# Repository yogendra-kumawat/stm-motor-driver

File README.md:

# MotorCore-32 v1.0
### STM32 Motor Control Carrier Board

> A modular carrier board for the Blue Pill STM32F103 module — dual DRV8833 H-bridge motor drivers, onboard power management, fault indication, and full GPIO breakout. Designed for robotics, automation, and embedded motor control projects.

---

## Board Preview

<!--  board photos -->
```
[ Top view photo ]         [ Bottom view photo ]
```
> *Photos will be added after fabrication*

---

## Features

| Feature | Details |
|---|---|
| MCU Module | Blue Pill (STM32F103C8T6) via female headers |
| Motor Drivers | 2× DRV8833PW — 1.5A per channel, dual H-bridge |
| Motor Outputs | 4× 2-pin screw terminals |
| 3.3V Rail | AMS1117-3.3 onboard regulator |
| Adjustable Rail | LM317 with external resistor headers |
| Input Voltage | 9V DC, 2A minimum |
| Reverse Polarity | 1N4007 diode protection |
| Spike Protection | SMBJ9.0CA TVS diode |
| Fault Indication | nFAULT LED per DRV8833 |
| GPIO Breakout | 2× 20-pin male headers — full Blue Pill pin access |

---

## Pin Map

### Power Rails

| Rail | Source | Voltage | Max Current |
|---|---|---|---|
| VMOT | Direct input after TVS | 9V | Input limited |
| 3.3V | AMS1117-3.3 | 3.3V | 800mA |
| VADJ | LM317 adjustable | User set | 1.5A |
| GND | Common ground | 0V | — |

### LM317 Adjust Header (J_ADJ)

| Pin | Signal |
|---|---|
| 1 | OUT |
| 2 | ADJ |
| 3 | R1 (connect 240Ω) |
| 4 | GND (connect R2 here) |

**Vout formula:** `Vout = 1.25 × (1 + R2/R1)`

| R2 | Vout (R1 = 240Ω) |
|---|---|
| 470Ω | 3.7V |
| 750Ω | 5.0V |
| 1.2kΩ | 7.5V |
| 1.5kΩ | 9.0V |

### DRV8833 Motor Driver 1 (U1)

| Pin | Signal | Connect to |
|---|---|---|
| IN1 | Motor A direction 1 | STM32 PWM pin |
| IN2 | Motor A direction 2 | STM32 PWM pin |
| IN3 | Motor B direction 1 | STM32 PWM pin |
| IN4 | Motor B direction 2 | STM32 PWM pin |
| nSLEEP | Enable/Sleep | STM32 GPIO or pull HIGH |
| nFAULT | Fault output | LED indicator onboard |

### DRV8833 Motor Driver 2 (U2)

Same pinout as U1 — controls Motor C and Motor D.

---

## Schematic

<!-- Add schematic PDF export here -->
> Schematic exported from KiCad — see `/hardware/schematic.pdf`

---

## Power Architecture

```
Barrel Jack (9V DC, 2A)
        │
        ▼
   1N4007 Diode
   (reverse polarity)
        │
        ▼
  SMBJ9.0CA TVS
  (spike protection)
        │
        ├──────────────────────→ DRV8833 x2 VM pins (motor power)
        │
        ├──→ AMS1117-3.3 ──────→ 3.3V rail (STM32, ESP-01, logic)
        │
        └──→ LM317 (adj) ───────→ VADJ rail (user configurable)
```

---

## Motor Wiring

```
Motor A+  ──→  J_MOT1 Pin 1
Motor A-  ──→  J_MOT1 Pin 2
Motor B+  ──→  J_MOT2 Pin 1
Motor B-  ──→  J_MOT2 Pin 2
Motor C+  ──→  J_MOT3 Pin 1
Motor C-  ──→  J_MOT3 Pin 2
Motor D+  ──→  J_MOT4 Pin 1
Motor D-  ──→  J_MOT4 Pin 2
```

---

## Fault Indication

Each DRV8833 has a dedicated **nFAULT LED**:

- **LED OFF** → Normal operation
- **LED ON** → Fault detected (overcurrent or overtemperature)

DRV8833 pulls nFAULT LOW on fault. LED lights via active-low circuit with 3.3V pull-up and series resistor.

Connect nFAULT to STM32 GPIO interrupt pin for firmware fault handling.

---

## Getting Started

### 1. Power the board
Connect 9V DC 2A adapter to barrel jack. Power LED illuminates.

### 2. Plug in Blue Pill
Insert Blue Pill module into the 2× 20-pin female headers.

### 3. Connect motors
Wire DC motors to screw terminals J_MOT1 through J_MOT4.

### 4. Flash firmware
Connect ST-Link to SWD header and flash via STM32CubeIDE.

### 5. Control motors
Drive IN1–IN4 pins with PWM from STM32 to control speed and direction.

---

## Firmware Example (STM32 HAL)

```c
// Motor A forward at 50% speed
HAL_GPIO_WritePin(GPIOA, IN1_PIN, GPIO_PIN_SET);
HAL_GPIO_WritePin(GPIOA, IN2_PIN, GPIO_PIN_RESET);
__HAL_TIM_SET_COMPARE(&htim2, TIM_CHANNEL_1, 500); // 50% of 1000

// Motor A stop
HAL_GPIO_WritePin(GPIOA, IN1_PIN, GPIO_PIN_RESET);
HAL_GPIO_WritePin(GPIOA, IN2_PIN, GPIO_PIN_RESET);

// Check nFAULT
if (HAL_GPIO_ReadPin(GPIOA, NFAULT_PIN) == GPIO_PIN_RESET) {
    // Fault detected — handle error
}
```

---

## Design Decisions

**Why DRV8833 over L298N?**
DRV8833 is a modern TI IC with integrated flyback diodes, 0.6V voltage drop vs L298N's 3.6V, smaller footprint, and 1.5A per channel. L298N is a 1980s design with poor efficiency.

**Why TVS over zener for spike protection?**
Zener diodes cannot handle the peak current from motor switching transients. TVS diodes are rated for transient power absorption (600W for SMBJ series) and respond in picoseconds.

**Why LM317 adjustable instead of fixed 5V regulator?**
User-configurable output voltage makes the board reusable across different peripheral voltages without PCB modification.

---

## License

Open hardware — feel free to use, modify, and build upon this design.

---

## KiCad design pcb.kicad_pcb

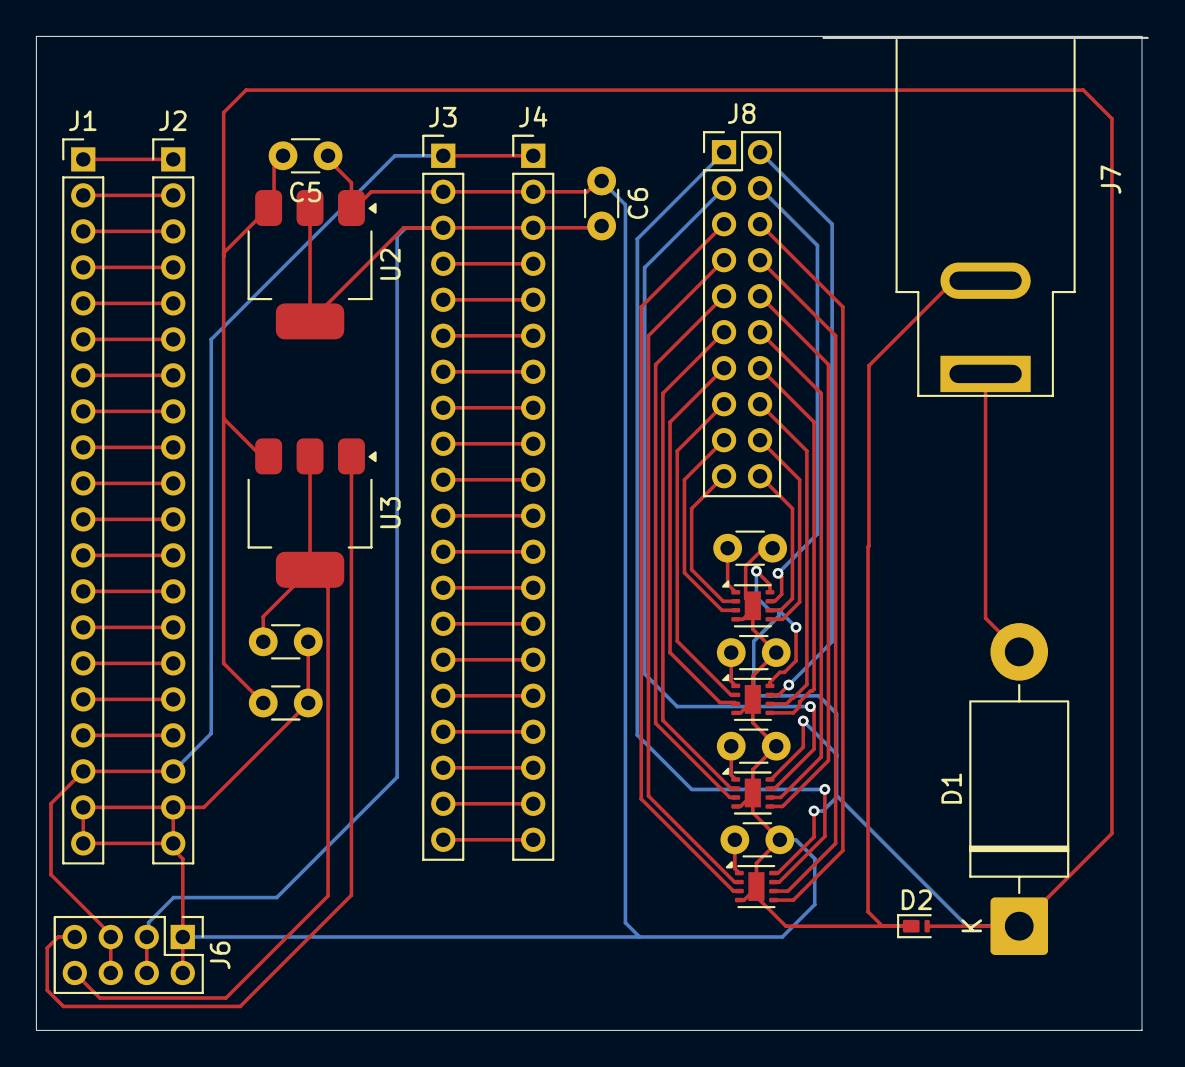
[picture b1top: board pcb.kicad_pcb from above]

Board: 2 copper layers, 61.4 x 55.2 mm, 23 parts (0 on the bottom side), 65 nets.

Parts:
C1, C2, C3, C4, C5, C6, C7, C8: C; C_Disc_D3.0mm_W1.6mm_P2.50mm
D1: 1N5400; D_DO-201AD_P15.24mm_Horizontal
D2: PTVS7V5Z1USK; Nexperia_DSN1608-2_1.6x0.8mm
J1, J2, J3, J4: Conn_01x20_Socket; PinHeader_1x20_P2.00mm_Vertical
J6: Conn_02x04_Odd_Even; PinHeader_2x04_P2.00mm_Vertical
J7: Barrel_Jack; BarrelJack_SwitchcraftConxall_RAPC10U_Horizontal
J8: Conn_02x10_Odd_Even; PinHeader_2x10_P2.00mm_Vertical
U1, U4, U5, U6: DRV8837C; WSON-8-1EP_2x2mm_P0.5mm_EP0.9x1.6mm
U2: AMS1117-5.0; SOT-223-3_TabPin2
U3: AMS1117; SOT-223-3_TabPin2

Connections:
/3.3V: J1.18, J2.18, J3.1, J4.1, J6.5, J6.6
/5V: C6.2, J3.3, J4.3, J6.3, J6.4, U2.2 (VO)
/ADJ: J6.7, U3.1 (ADJ)
/AD_OUT: C8.2, J6.8, U3.2 (VO)
/GND: C1.2, C2.2, C3.2, C4.2, C5.1, C6.1, C7.1, C8.1, D2.1 (K), J1.19, J1.20, J2.19, J2.20, J3.2, J4.2, J6.1, J6.2, J7.2, U1.4 (GND), U1.9 (GND), U2.1 (GND), U4.4 (GND), U4.9 (GND), U5.4 (GND), U5.9 (GND), U6.4 (GND), U6.9 (GND)
/MI1A: J8.20, U4.6 (IN1)
/MI1B: J8.18, U4.5 (IN2)
/MI2A: J8.16, U5.6 (IN1)
/MI2B: J8.14, U5.5 (IN2)
/MI3A: J8.12, U1.6 (IN1)
/MI3B: J8.10, U1.5 (IN2)
/MI4A: J8.8, U6.6 (IN1)
/MI4B: J8.6, U6.5 (IN2)
/MO1A: J8.19, U4.2 (OUT1)
/MO1B: J8.17, U4.3 (OUT2)
/MO2A: J8.15, U5.2 (OUT1)
/MO2B: J8.13, U5.3 (OUT2)
/MO3A: J8.11, U1.2 (OUT1)
/MO3B: J8.9, U1.3 (OUT2)
/MO4A: J8.7, U6.2 (OUT1)
/MO4B: J8.5, U6.3 (OUT2)
/S1: J8.4, U4.7 (~SLEEP)
/S2: J8.2, U5.7 (~SLEEP)
/S3: J8.1, U6.7 (~SLEEP)
/S4: J8.3, U1.7 (~SLEEP)
/VIN: C5.2, C7.2, D1.1 (K), D2.2 (A), U1.8 (VCC), U2.3 (VI), U3.3 (VI), U4.8 (VCC), U5.8 (VCC), U6.8 (VCC)
unnamed: D1.2 (A), J7.1
unnamed: J1.1, J2.1
unnamed: J1.2, J2.2
unnamed: J1.3, J2.3
unnamed: J1.4, J2.4
unnamed: J1.5, J2.5
unnamed: J1.6, J2.6
unnamed: J1.7, J2.7
unnamed: J1.8, J2.8
unnamed: J1.9, J2.9
unnamed: J1.10, J2.10
unnamed: J1.11, J2.11
unnamed: J1.12, J2.12
unnamed: J1.13, J2.13
unnamed: J1.14, J2.14
unnamed: J1.15, J2.15
unnamed: J1.16, J2.16
unnamed: J1.17, J2.17
unnamed: J3.4, J4.4
unnamed: J3.5, J4.5
unnamed: J3.6, J4.6
unnamed: J3.7, J4.7
unnamed: J3.8, J4.8
unnamed: J3.9, J4.9
unnamed: J3.10, J4.10
unnamed: J3.11, J4.11
unnamed: J3.12, J4.12
unnamed: J3.13, J4.13
unnamed: J3.14, J4.14
unnamed: J3.15, J4.15
unnamed: J3.16, J4.16
unnamed: J3.17, J4.17
unnamed: J3.18, J4.18
unnamed: J3.19, J4.19
unnamed: J3.20, J4.20
unnamed: C3.1, U1.1 (VM)
unnamed: C4.1, U4.1 (VM)
unnamed: C1.1, U5.1 (VM)
unnamed: C2.1, U6.1 (VM)
